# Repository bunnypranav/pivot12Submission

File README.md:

# PIVOT 12

PIVOT 12 is a macropad with 10 MX switches and two rotary encoders and uses QMK firmware. It is aimed for productivity with a huge focus on the two dials. The name "PIVOT" signifies the rotary encoders as "pivotal" control elements (*pun intended*). The "12" in the name refers to the total number of inputs (10 switches + 2 rotary encoders) on the macropad.

A lot of what I do involves switching tabs, scrolling, navigating files, adjusting volume, and triggering similar shortcuts. Instead of just keys, I wanted something that felt like a control panel, and that is where the two dials come in. One usually handles navigation (like horizontal scrolling or tab switching), and the other handles adjustments (volume, zoom, etc.). Each encoder also has a push button, so they're more than just scroll wheels.

Building this was a great learning experience. I designed the PCB in KiCad and the case in Fusion 360. It was my first time designing a PCB, and I definitely struggled, and learned a lot. The case design was also a fun challenge, especially with the incline and making sure everything fit properly and was compatible with the PCB.

# Features
* 10 MX switches
* 2 Rotary Encoders
* Case with a 7° incline for ergonomic use

# PCB
*Made in KiCad*

# CAD Model
*Made in Fusion 360*
I didn't want a flat box, so I added a 7° incline. It's subtle, but it makes a noticeable difference when using it for long periods. The incline feels natural without making the device bulky.

For a video, see https://github.com/bunnypranav/pivot12Submission/raw/refs/heads/main/images/caseVid.mp4

# BOM:
* 1x XIAO RP2040
* 10x Cherry MX Switches
* 10x DSA Keycaps
* 2x EC11 Rotary Encoder
* 12x 1N4148 DO-35 Diodes.
* 4x M3x5x4 Heatset inserts
* 4x M3x16mm SHCS Bolts
* 1x PCB: Costs about USD 14 with shipping
* 1x Case (4 printed parts)
  * Bottom base
  * Top plate
  * 2x Knurled knobs for dials

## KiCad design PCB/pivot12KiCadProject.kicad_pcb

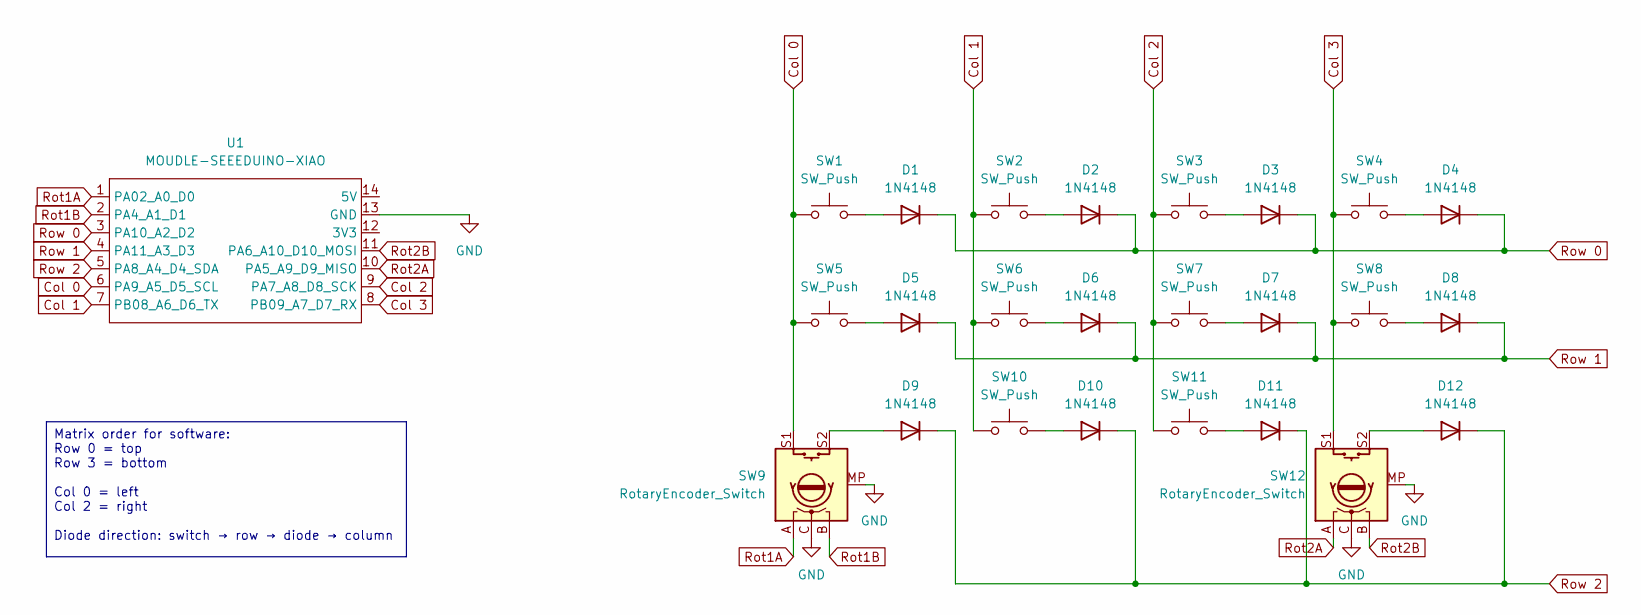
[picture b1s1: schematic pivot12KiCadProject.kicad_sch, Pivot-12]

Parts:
D1, D2, D3, D4, D5, D6, D7, D8, D9, D10, D11, D12: 1N4148; D_DO-35_SOD27_P7.62mm_Horizontal
SW1, SW2, SW3, SW4, SW5, SW6, SW7, SW8, SW10, SW11: SW_Push; SW_Cherry_MX_1.00u_PCB
SW9, SW12: RotaryEncoder_Switch; RotaryEncoder_Alps_EC11E-Switch_Vertical_H20mm
U1: MOUDLE-SEEEDUINO-XIAO; XIAO-Generic-Hybrid-14P-2.54-21X17.8MM

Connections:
Col 0: SW1.1, SW5.1, SW9.S1, U1.6 (PA9_A5_D5_SCL)
Col 1: SW2.1, SW6.1, SW10.1, U1.7 (PB08_A6_D6_TX)
Col 2: SW3.1, SW7.1, SW11.1, U1.9 (PA7_A8_D8_SCK)
Col 3: SW4.1, SW8.1, SW12.S1, U1.8 (PB09_A7_D7_RX)
GND: SW9.C, SW9.MP, SW12.C, SW12.MP, U1.13 (GND)
unnamed: D1.2 (A), SW1.2
unnamed: D2.2 (A), SW2.2
unnamed: D3.2 (A), SW3.2
unnamed: D4.2 (A), SW4.2
unnamed: D5.2 (A), SW5.2
unnamed: D6.2 (A), SW6.2
unnamed: D7.2 (A), SW7.2
unnamed: D8.2 (A), SW8.2
unnamed: D9.2 (A), SW9.S2
unnamed: D10.2 (A), SW10.2
unnamed: D11.2 (A), SW11.2
unnamed: D12.2 (A), SW12.S2
Rot1A: SW9.A, U1.1 (PA02_A0_D0)
Rot1B: SW9.B, U1.2 (PA4_A1_D1)
Rot2A: SW12.A, U1.10 (PA5_A9_D9_MISO)
Rot2B: SW12.B, U1.11 (PA6_A10_D10_MOSI)
Row 0: D1.1 (K), D2.1 (K), D3.1 (K), D4.1 (K), U1.3 (PA10_A2_D2)
Row 1: D5.1 (K), D6.1 (K), D7.1 (K), D8.1 (K), U1.4 (PA11_A3_D3)
Row 2: D9.1 (K), D10.1 (K), D11.1 (K), D12.1 (K), U1.5 (PA8_A4_D4_SDA)

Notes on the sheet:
Matrix order for software: Row 0 = top Row 3 = bottom Col 0 = left Col 2 = right Diode direction: switch → row → diode → column

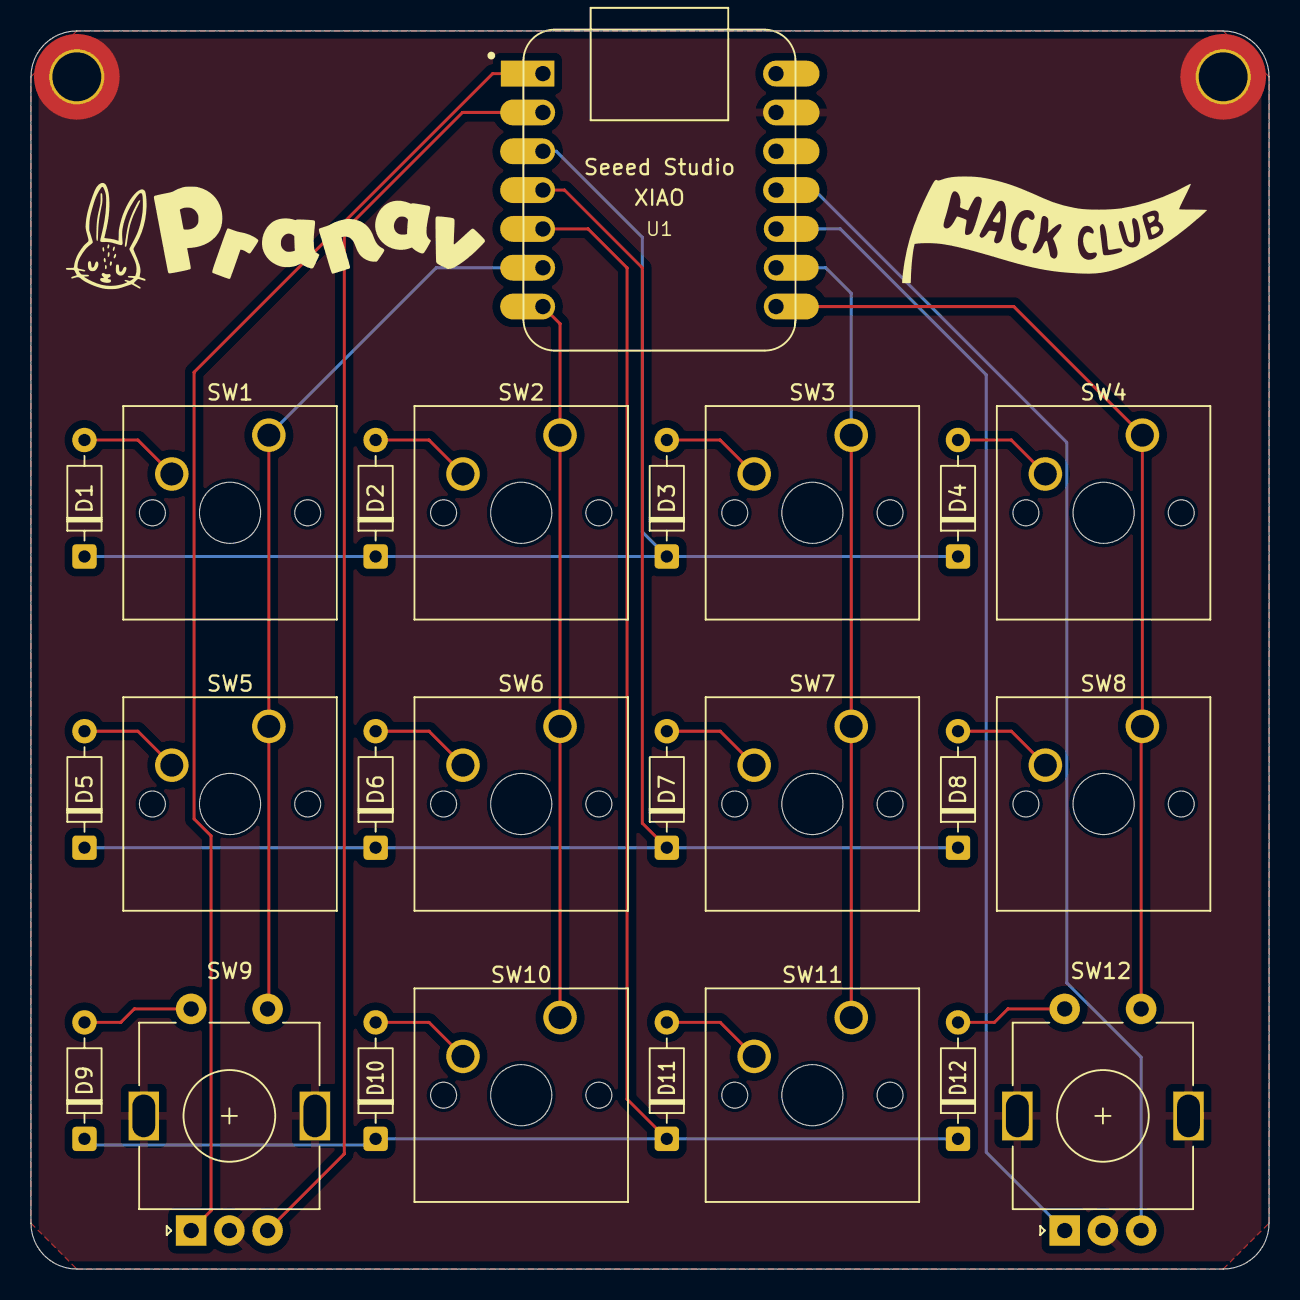
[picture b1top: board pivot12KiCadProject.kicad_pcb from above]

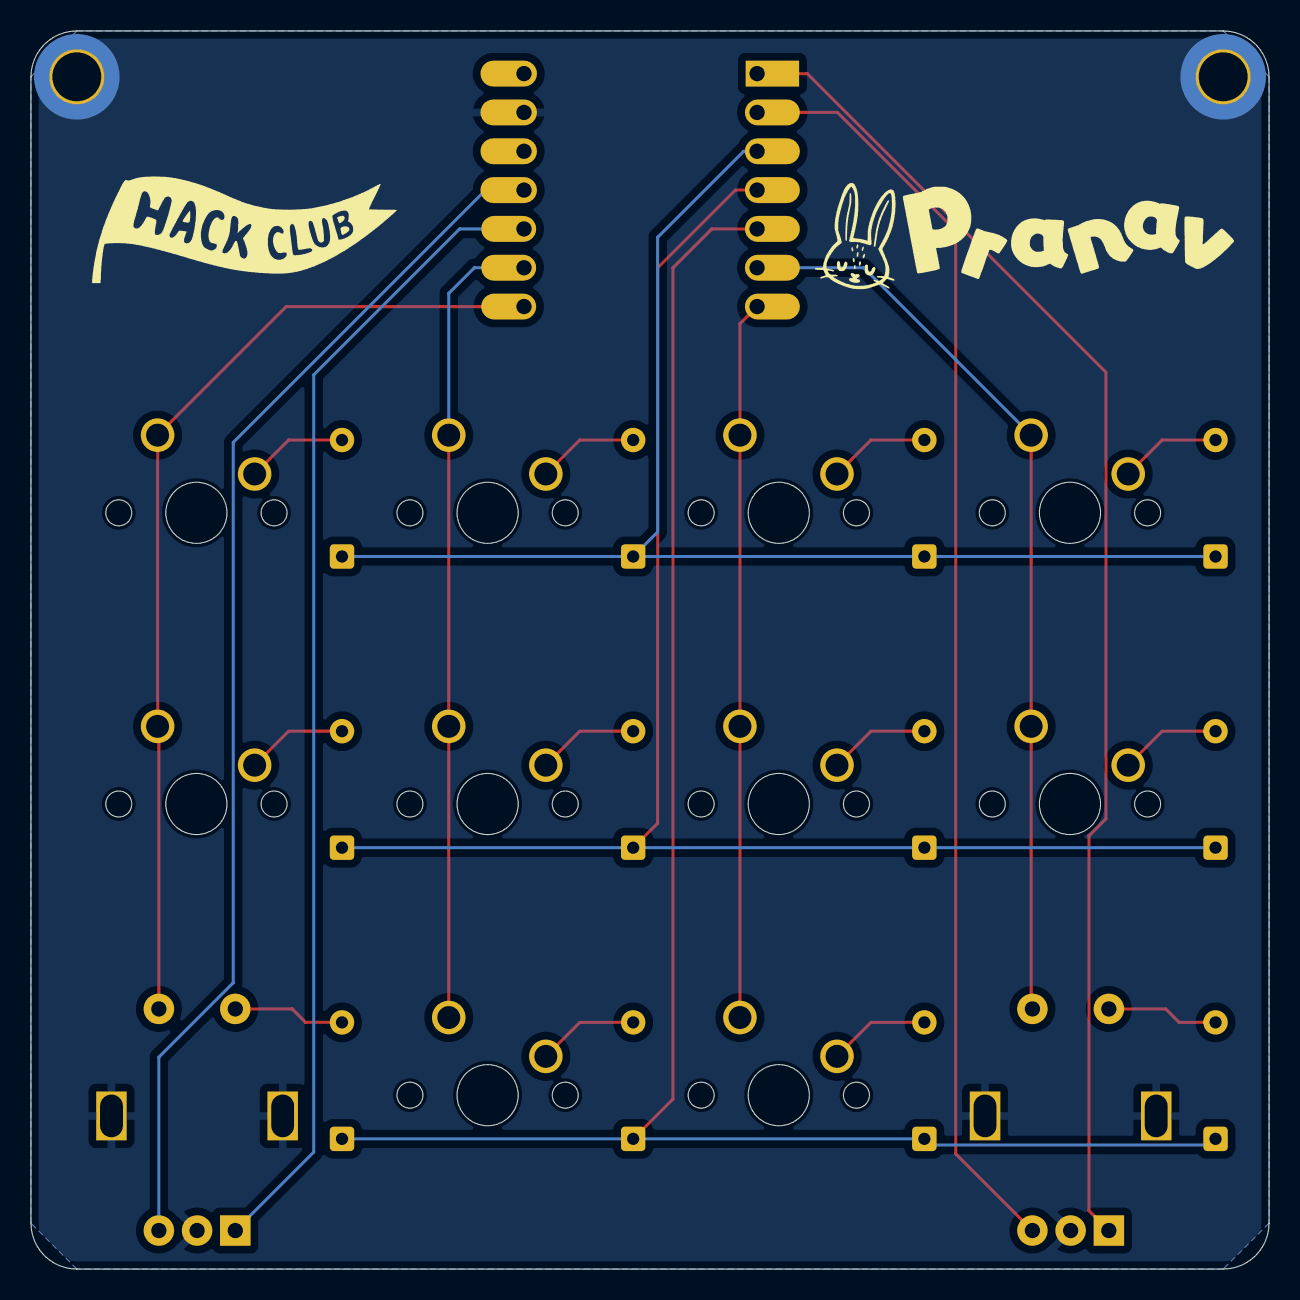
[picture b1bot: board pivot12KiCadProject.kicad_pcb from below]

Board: 2 copper layers, 81.0 x 81.0 mm, 29 parts (2 on the bottom side), 24 nets.

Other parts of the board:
Logo1, Logo1#2: LOGO
Mount2, Mount2#2: LOGO

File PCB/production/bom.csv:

Designator,Footprint,Quantity,Value,LCSC Part #
"D1, D10, D11, D12, D2, D3, D4, D5, D6, D7, D8, D9",D_DO-35_SOD27_P7.62mm_Horizontal,12,1N4148,
"SW1, SW10, SW11, SW2, SW3, SW4, SW5, SW6, SW7, SW8",SW_Cherry_MX_1.00u_PCB,10,SW_Push,
"SW12, SW9",RotaryEncoder_Alps_EC11E-Switch_Vertical_H20mm,2,RotaryEncoder_Switch,
U1,XIAO-Generic-Hybrid-14P-2.54-21X17.8MM,1,MOUDLE-SEEEDUINO-XIAO,

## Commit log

2026-02-13 Add CAD with full PCB, STEP file, and related images in README
2026-05-21 Update with new firmware and built photos
